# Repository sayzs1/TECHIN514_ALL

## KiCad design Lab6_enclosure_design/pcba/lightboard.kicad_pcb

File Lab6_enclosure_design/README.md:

Welcome to the enclosure design lab.  You'll make a simple enclosure for your PCB, similar to the example.

To transfer data from the PCB program into Fusion we'll use a STEP file which is a common format for 3D interchange that will maintain geometry and dimensions and works for multi-part assemblies.  For the PCB you can export a STEP file from KiCAD (recommended to try this yourself) or just use the STEP file in the repository. 

Build an enclosure similar to the example we will show during the lecture.  It must :

    Be your own design !
    Support the PCB with features to fasten in place
    Have flexure or other secondary part that allows the button to be pressed
    Have a window or other feature that allows you to see the LED
    Have a unique identifying feature (your name, or a logo embossed into the device)

For reference you can look at the example Fusion file in this repo.  I recommend using the timeline feature of Fusion to roll back and look at individual steps.  There are many ways to build a model, so its totally OK if you approach it differently.

When you're finished, upload to canvas : 

Your Fusion file (F3D)

A STEP export file of your parts

Section views as described in the rubric (screenshot is OK)

    main cross-section view showing joints between parts
    
    section or detail view to show your LED viewing feature
    
    3D AND section views showing the button feature
    
    3D views of complete device

For details of what must be uploaded to canvas, please consult the assignment rubric (which will always take precedence)

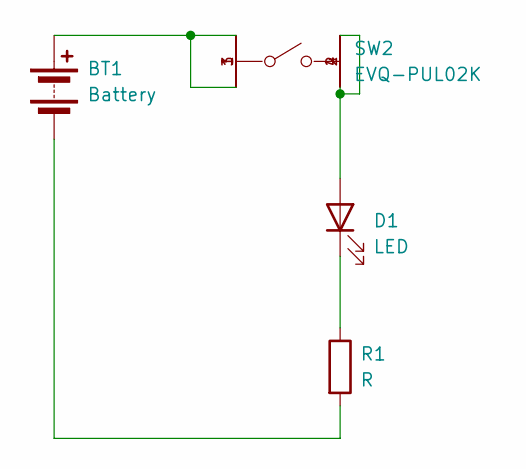
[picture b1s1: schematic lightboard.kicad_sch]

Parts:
BT1: Battery; BatteryHolder_Multicomp_BC-2001_1x2032
D1: LED; LED_0805_2012Metric
R1: R; R_0805_2012Metric
SW2: EVQ-PUL02K; Panasonic-EVQ-PUL02K-0; mouser part number 667-EVQ-PUL02K; digikey description SWITCH TACTILE SPST-NO 0.05A 12V

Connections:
unnamed: BT1.1 (+), SW2.1, SW2.3
unnamed: BT1.2 (-), R1.2
unnamed: D1.2 (A), SW2.2, SW2.4
unnamed: D1.1 (K), R1.1

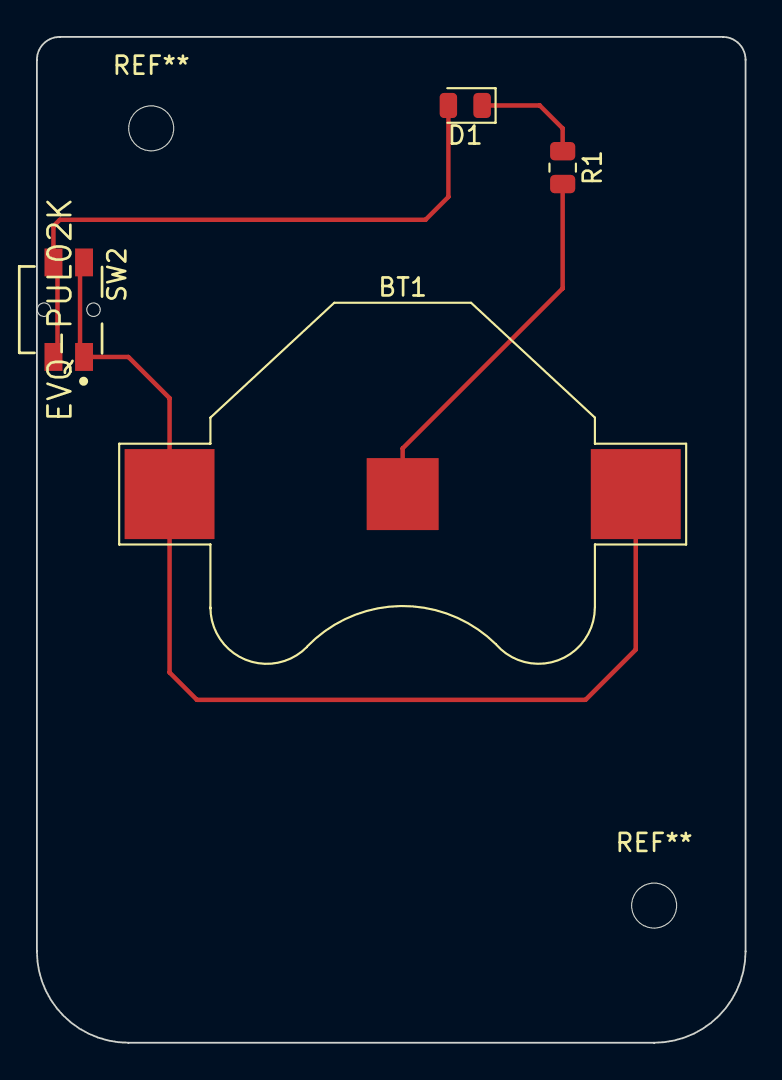
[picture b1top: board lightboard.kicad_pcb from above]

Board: 2 copper layers, 39.4 x 55.9 mm, 4 parts (0 on the bottom side), 4 nets.

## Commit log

2024-01-31 Add HC-SR04 sensor's symbol and footprint
2024-01-31 Init Lab 5 power management project
2024-01-31 Fulfill the 4-stage battery consumption exp
2024-01-31 Use customized inveral for each stage
2024-01-31 Init Lab 5 readme
2024-01-31 Add Lab 5 instructions
2024-01-31 Fix code typo in Lab 5 instructions
2024-01-31 Add WiFi disconnection and retry maximum handling
2024-02-01 Better clarifying the requirements of lab5
2024-02-06 Edit the typo of expected value in section 7
2024-02-07 added enclosure lab
2024-02-17 Init lab7 TinyML camera-using scripts
2024-02-17 Uploading the camera-captured image to Firebase
2024-02-21 Code changes to capture and upload imgs with switch
2024-02-21 chore : link fix
2024-02-21 updated camera config for lower resolution
2024-02-21 Add model deployment project backbone
2024-02-21 Init Lab 7 README
2024-02-21 Update test dataset
2024-02-21 Clean README contents and headers
2024-02-21 Add internal and external links
2024-02-21 Add submission notes
2024-02-21 Update submission requirements
